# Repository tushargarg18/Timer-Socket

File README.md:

# Timer-Socket
It is a plug in device, that closes any load device connected to it after a set timer. For the purpose of generating delay CMOS timer ic  CD4060 is used and a SMPS power supply is designed to power up the 5v DC circuit devices all packed in a small PCB
Here is the designed double sided PCB.

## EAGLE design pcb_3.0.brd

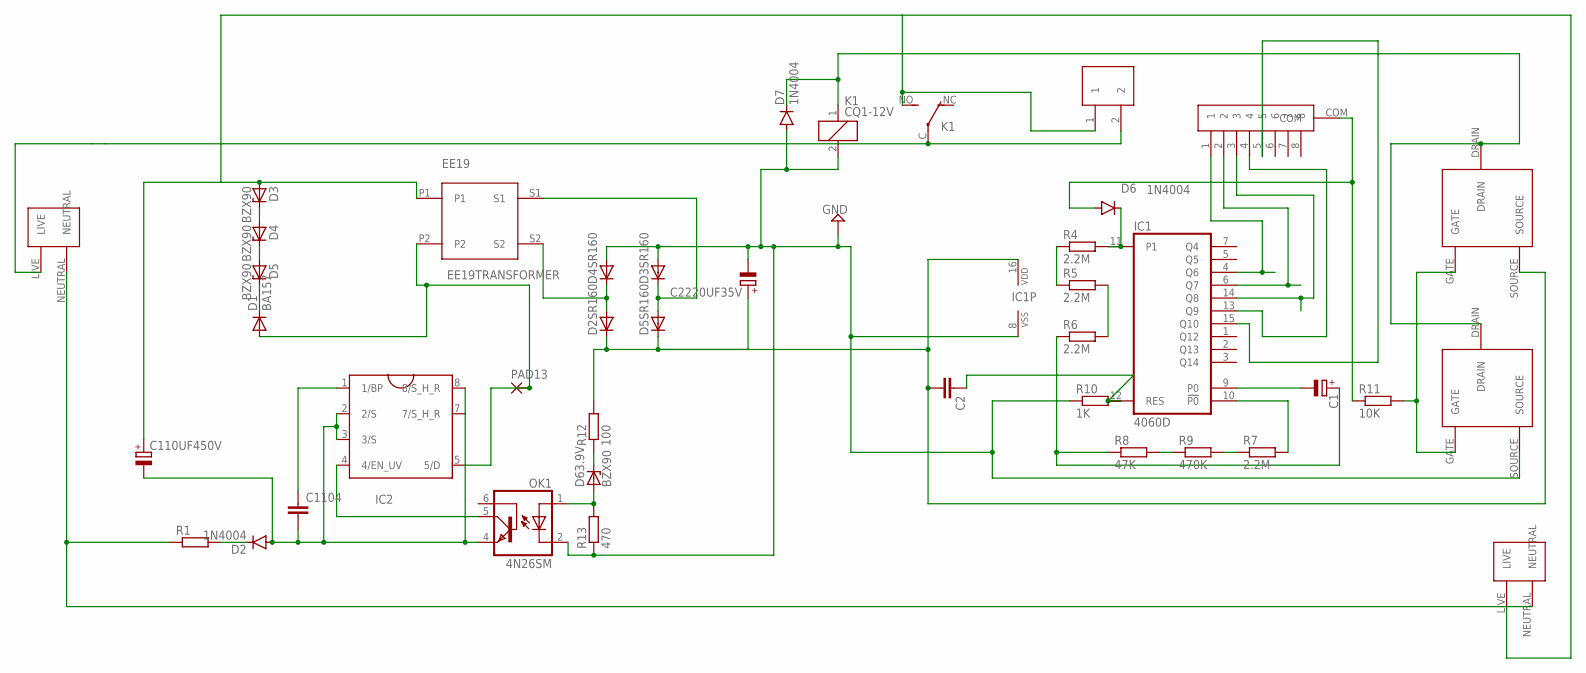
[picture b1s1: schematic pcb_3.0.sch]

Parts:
C1: CPOL-EUE2.5-6; E2,5-6
C2: C-EU025-025X050; C025-025X050
C110UF450V: CPOL-EUE5-10.5; E5-10,5
C1104: C-EU025-024X044; C025-024X044
C2220UF35V: CPOL-EUE3.5-8; E3,5-8
D1: BA157; P1-10
D2, D6, D7: 1N4004; DO41-10
D2SR160, D3SR160, D4SR160, D5SR160: DIODE_E-DO35-7; DIODE_DO35-7
D3, D4, D5, D63.9V: BZX90; DO34Z7
IC1: 4060D; SO16
IC2: TNY263-268; DIP8B_SMD(G_PACKAGE)
K1: CQ1-12V; CQ1
OK1: 4N26SM; DIL6-SMD
PAD13: 2,15/1,0
R1: R-EU_0207/10; 0207/10
R4, R5, R6, R7: 2.2M; 0204/5
R8: 47K; 0204/5
R9: 470K; 0204/5
R10: 1K; 0204/5
R11: 10K; 0204/5
R12: 100; 0204/5
R13: 470; 0204/5
U$1: EE19TRANSFORMER; EE19
U$2, U$3: FR9024N
U$4, U$5: AC_INPUT
U$6: AC_PUSH_BUTTON
U$7: SINGLE_POLE_5_TRS; SINGLE_POLE_8_TRS

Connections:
GND: C2220UF35V.-, D3SR160.A (C), D4SR160.A (C), D7.A, IC1.8 (VSS), K1.2, OK1.2 (C), R10.1, R13.1, U$2.SOURCE
unnamed: D3.C, D4.A
unnamed: D2.C, R1.2
unnamed: IC1.4 (Q6), U$7.1
unnamed: D63.9V.A, OK1.1 (A), R13.2
unnamed: D1.A, IC2.5 (5/D), PAD13.1, U$1.P2
unnamed: D63.9V.C, R12.1
unnamed: D2SR160.A (C), D4SR160.C (A), U$1.S2
unnamed: C2.2, C2220UF35V.+, D2SR160.C (A), D5SR160.C (A), IC1.16 (VDD), R12.2, U$3.SOURCE
unnamed: R11.2, U$2.GATE, U$3.GATE
unnamed: D3SR160.C (A), D5SR160.A (C), U$1.S1
unnamed: IC2.4 (4/EN_UV), OK1.5 (COL)
unnamed: C1104.1, IC2.1 (1/BP)
unnamed: C110UF450V.-, C1104.2, D2.A, IC2.2 (2/S), IC2.3 (3/S), IC2.7 (7/S_H_R), IC2.8 (8/S_H_R), OK1.4 (EMI)
unnamed: D6.C, IC1.11 (P1), R4.2
unnamed: D4.C, D5.A
unnamed: D1.C, D5.C
unnamed: R4.1, R5.1
unnamed: R5.2, R6.2
unnamed: IC1.10 (!P0), R7.2
unnamed: R7.1, R9.2
unnamed: R8.2, R9.1
unnamed: C1.+, R6.1, R8.1
unnamed: IC1.6 (Q7), U$7.2
unnamed: IC1.14 (Q8), U$7.3
unnamed: IC1.13 (Q9), U$7.4
unnamed: IC1.15 (Q10), U$7.5
unnamed: D6.A, R11.1, U$7.COM
unnamed: D7.C, K1.1, U$2.DRAIN, U$3.DRAIN
unnamed: C110UF450V.+, D3.A, K1.NO (S), U$1.P1, U$5.LIVE, U$6.1
unnamed: C1.-, IC1.9 (P0)
unnamed: C2.1, IC1.12 (RES), R10.2
unnamed: K1.C, U$4.LIVE, U$6.2
unnamed: R1.1, U$4.NEUTRAL, U$5.NEUTRAL

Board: 2 copper layers, 40 parts (0 on the bottom side), 34 nets, no tracks yet.

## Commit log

2020-04-12 Add files via upload
    This the PCB schematic and Layout.
